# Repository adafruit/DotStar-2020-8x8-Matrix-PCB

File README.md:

## Adafruit DotStar High Density 8x8 Grid - 64 RGB LED Pixel Matrix PCB

<a href="http://www.adafruit.com/products/3444"><br/>
Click here to purchase one from the Adafruit shop</a>

PCB files for the Adafruit DotStar High Density 8x8 Grid - 64 RGB LED Pixel Matrix. Format is EagleCAD schematic and board layout
* https://www.adafruit.com/product/3444

### Description

Do not eat this LED grid just because it is so colorful and bite-sized! This is the tiniest little LED grid we could make, with 64 full RGB color pixels in a square that is only 1" by 1" square (thats 25.4mm x 25.4mm for you metric-lovers). Best of all, these are little DotStar LEDs, with built in PWM drivers, so you only need two digital I/O pins to get a-glowin'.

But do not be fooled by their small size, each LED is still incredibly, blindingly bright just like the DotStars/NeoPixels you know and love. These are the same integrated LEDs that are used in [our new fancy DotStar strips](https://www.adafruit.com/categories/885) just really small.

Arranged in an 8x8 matrix, each pixel is individually addressable: like NeoPixels, DotStar LEDs have an embedded microcontroller **inside the LED**. You can set the color/brightness of each LED to 24-bit color (8 bits each red green and blue). Each LED acts like a shift register, reading incoming color data on the input pins, and then shifting the previous color data out on the output pin. By sending a long string of data, you can control an 'infinite' number of LEDs. The PWM is built into each LED-chip so once you set the color you can stop talking to the disk and it will continue to PWM all the LEDs for you.

Wiring it up is easy: there are two 4-pad connection ports on the back. Solder wires to the input port (+5V GND ClockIn and DataIn) and provide 5VDC to the +5V and ground pins, then connect the CIN/DIN pin to your microcontroller. If you have hardware SPI, use the SCK and MOSI pins respectively. You'll also need to make a common ground from the 5V power supply to the microcontroller/Arduino. Since each LED can draw as much as 40mA (thats up to 2.5 Amps per panel if all LEDs are on bright white!) we suggest our 5V 2A power supply if you're going to use full brightness and a lot of white. For most uses, you'll see about 0.5A of current per panel, and you can set the brightness to drop that down. Note that so much current through a small board can make it toasty!

To keep the board small, we did not put any small surface-mount capacitors on the front. Instead, there's a power/ground pad set on the back and a 220uF capacitor that you can solder onto the back for a compact fit. There's also four mounting holes that you can use for attachment, or snap them off with pliers if you want a perfect 1" square.

[Check out our tutorial showing wiring, power usage calculations, example code for usage, etc!](https://learn.adafruit.com/adafruit-dotstar-leds)

### License

Adafruit invests time and resources providing this open source design, please support Adafruit and open-source hardware by purchasing products from [Adafruit](https://www.adafruit.com)!

Designed by Limor Fried/Ladyada for Adafruit Industries.

Creative Commons Attribution/Share-Alike, all text above must be included in any redistribution. See license.txt for additional details.

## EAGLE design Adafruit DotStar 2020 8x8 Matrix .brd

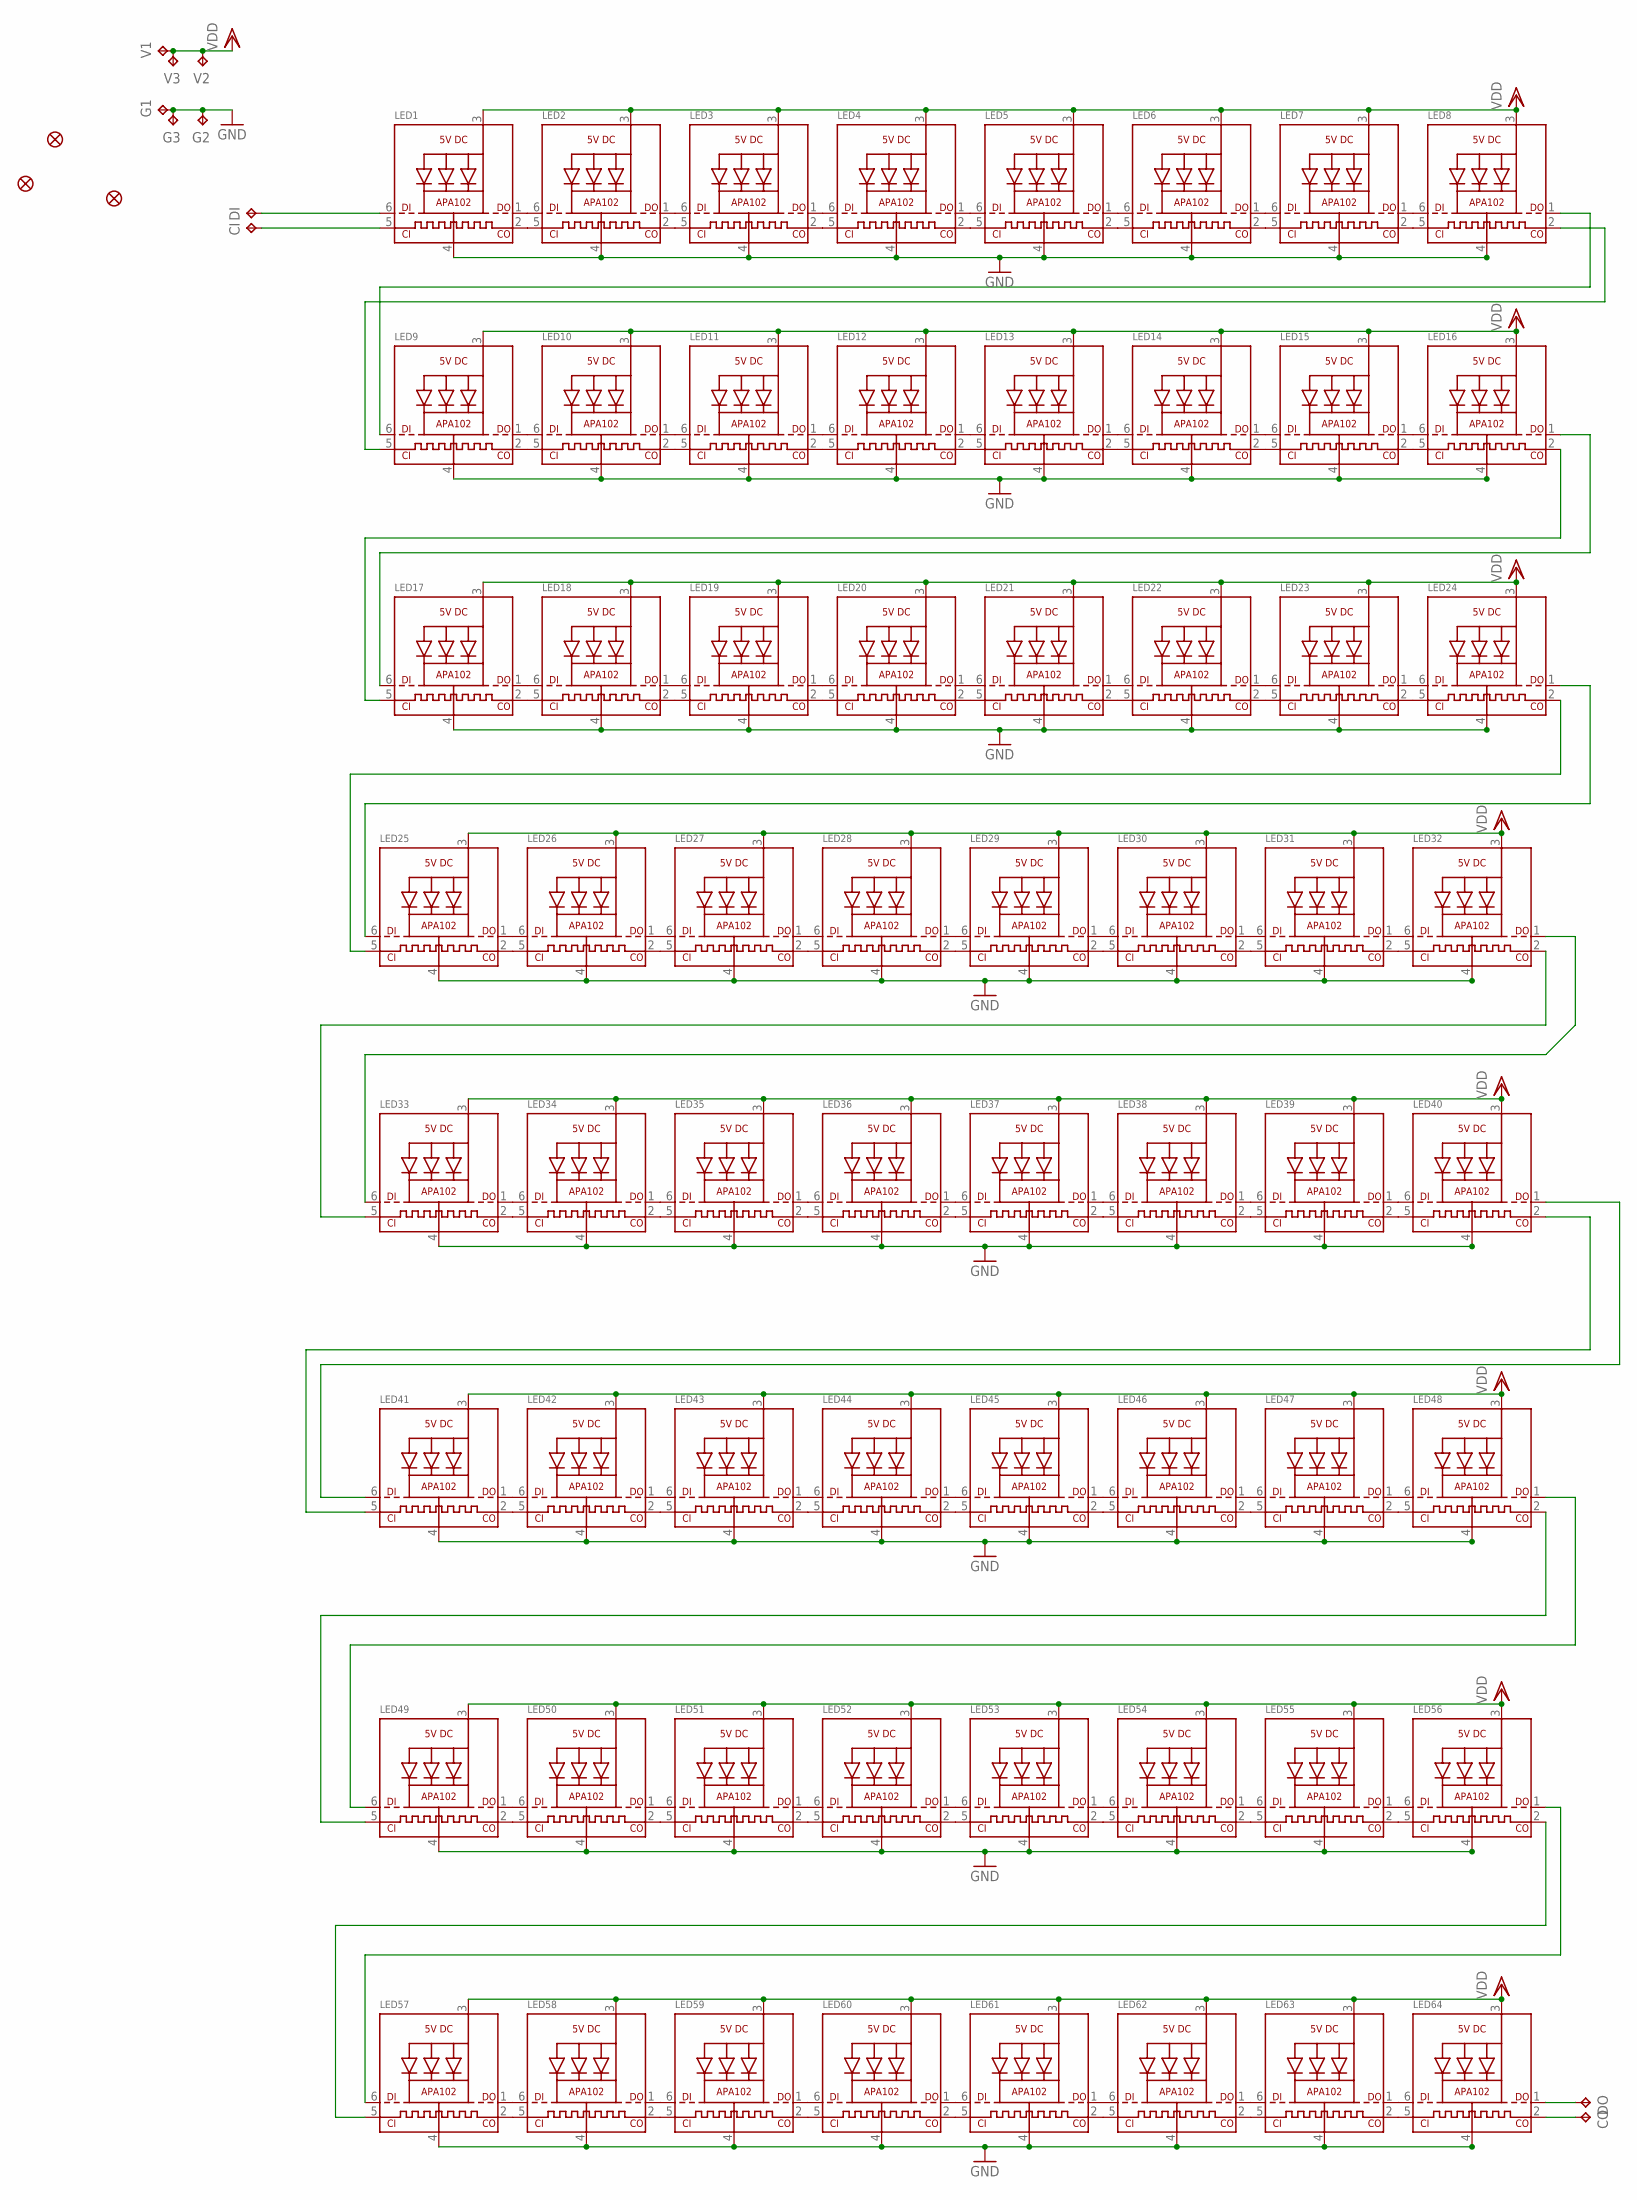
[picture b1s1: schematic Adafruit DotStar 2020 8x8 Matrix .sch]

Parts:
CI: TPTP20R; TP20R
CO: TPTP20R; TP20R
DI: TPTP20R; TP20R
DO: TPTP20R; TP20R
FID1, FID2, FID3: FIDUCIAL_0.5MM
G1, G2, G3: TPTP20R; TP20R
LED1, LED2, LED3, LED4, LED5, LED6, LED7, LED8, LED9, LED10, LED11, LED12, LED13, LED14, LED15, LED16, LED17, LED18, LED19, LED20, LED21, LED22, LED23, LED24, LED25, LED26, LED27, LED28, LED29, LED30, LED31, LED32, LED33, LED34, LED35, LED36, LED37, LED38, LED39, LED40, LED41, LED42, LED43, LED44, LED45, LED46, LED47, LED48, LED49, LED50, LED51, LED52, LED53, LED54, LED55, LED56, LED57, LED58, LED59, LED60, LED61, LED62, LED63, LED64: APA1022020; APA102_2020
V1, V2, V3: TPTP20R; TP20R

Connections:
C0: CO.TP, LED64.2 (CKO)
CIN: CI.TP, LED1.5 (CKI)
D0: DO.TP, LED64.1 (DO)
DIN: DI.TP, LED1.6 (DI)
GND: G1.TP, G2.TP, G3.TP, LED1.4 (GND), LED2.4 (GND), LED3.4 (GND), LED4.4 (GND), LED5.4 (GND), LED6.4 (GND), LED7.4 (GND), LED8.4 (GND), LED9.4 (GND), LED10.4 (GND), LED11.4 (GND), LED12.4 (GND), LED13.4 (GND), LED14.4 (GND), LED15.4 (GND), LED16.4 (GND), LED17.4 (GND), LED18.4 (GND), LED19.4 (GND), LED20.4 (GND), LED21.4 (GND), LED22.4 (GND), LED23.4 (GND), LED24.4 (GND), LED25.4 (GND), LED26.4 (GND), LED27.4 (GND), LED28.4 (GND), LED29.4 (GND), LED30.4 (GND), LED31.4 (GND), LED32.4 (GND), LED33.4 (GND), LED34.4 (GND), LED35.4 (GND), LED36.4 (GND), LED37.4 (GND), LED38.4 (GND), LED39.4 (GND), LED40.4 (GND), LED41.4 (GND), LED42.4 (GND), LED43.4 (GND), LED44.4 (GND), LED45.4 (GND), LED46.4 (GND), LED47.4 (GND), LED48.4 (GND), LED49.4 (GND), LED50.4 (GND), LED51.4 (GND), LED52.4 (GND), LED53.4 (GND), LED54.4 (GND), LED55.4 (GND), LED56.4 (GND), LED57.4 (GND), LED58.4 (GND), LED59.4 (GND), LED60.4 (GND), LED61.4 (GND), LED62.4 (GND), LED63.4 (GND), LED64.4 (GND)
unnamed: LED1.1 (DO), LED2.6 (DI)
unnamed: LED1.2 (CKO), LED2.5 (CKI)
unnamed: LED2.1 (DO), LED3.6 (DI)
unnamed: LED2.2 (CKO), LED3.5 (CKI)
unnamed: LED3.1 (DO), LED4.6 (DI)
unnamed: LED3.2 (CKO), LED4.5 (CKI)
unnamed: LED4.1 (DO), LED5.6 (DI)
unnamed: LED4.2 (CKO), LED5.5 (CKI)
unnamed: LED5.1 (DO), LED6.6 (DI)
unnamed: LED5.2 (CKO), LED6.5 (CKI)
unnamed: LED6.1 (DO), LED7.6 (DI)
unnamed: LED6.2 (CKO), LED7.5 (CKI)
unnamed: LED7.1 (DO), LED8.6 (DI)
unnamed: LED7.2 (CKO), LED8.5 (CKI)
unnamed: LED9.1 (DO), LED10.6 (DI)
unnamed: LED9.2 (CKO), LED10.5 (CKI)
unnamed: LED10.1 (DO), LED11.6 (DI)
unnamed: LED10.2 (CKO), LED11.5 (CKI)
unnamed: LED11.1 (DO), LED12.6 (DI)
unnamed: LED11.2 (CKO), LED12.5 (CKI)
unnamed: LED12.1 (DO), LED13.6 (DI)
unnamed: LED12.2 (CKO), LED13.5 (CKI)
unnamed: LED13.1 (DO), LED14.6 (DI)
unnamed: LED13.2 (CKO), LED14.5 (CKI)
unnamed: LED14.1 (DO), LED15.6 (DI)
unnamed: LED14.2 (CKO), LED15.5 (CKI)
unnamed: LED15.1 (DO), LED16.6 (DI)
unnamed: LED15.2 (CKO), LED16.5 (CKI)
unnamed: LED17.1 (DO), LED18.6 (DI)
unnamed: LED17.2 (CKO), LED18.5 (CKI)
unnamed: LED18.1 (DO), LED19.6 (DI)
unnamed: LED18.2 (CKO), LED19.5 (CKI)
unnamed: LED19.1 (DO), LED20.6 (DI)
unnamed: LED19.2 (CKO), LED20.5 (CKI)
unnamed: LED20.1 (DO), LED21.6 (DI)
unnamed: LED20.2 (CKO), LED21.5 (CKI)
unnamed: LED21.1 (DO), LED22.6 (DI)
unnamed: LED21.2 (CKO), LED22.5 (CKI)
unnamed: LED22.1 (DO), LED23.6 (DI)
unnamed: LED22.2 (CKO), LED23.5 (CKI)
unnamed: LED23.1 (DO), LED24.6 (DI)
unnamed: LED23.2 (CKO), LED24.5 (CKI)
unnamed: LED25.1 (DO), LED26.6 (DI)
unnamed: LED25.2 (CKO), LED26.5 (CKI)
unnamed: LED26.1 (DO), LED27.6 (DI)
unnamed: LED26.2 (CKO), LED27.5 (CKI)
unnamed: LED27.1 (DO), LED28.6 (DI)
unnamed: LED27.2 (CKO), LED28.5 (CKI)
unnamed: LED28.1 (DO), LED29.6 (DI)
unnamed: LED28.2 (CKO), LED29.5 (CKI)
unnamed: LED29.1 (DO), LED30.6 (DI)
unnamed: LED29.2 (CKO), LED30.5 (CKI)
unnamed: LED30.1 (DO), LED31.6 (DI)
unnamed: LED30.2 (CKO), LED31.5 (CKI)
unnamed: LED31.1 (DO), LED32.6 (DI)
unnamed: LED31.2 (CKO), LED32.5 (CKI)
unnamed: LED33.1 (DO), LED34.6 (DI)
unnamed: LED33.2 (CKO), LED34.5 (CKI)
unnamed: LED34.1 (DO), LED35.6 (DI)
unnamed: LED34.2 (CKO), LED35.5 (CKI)
unnamed: LED35.1 (DO), LED36.6 (DI)
unnamed: LED35.2 (CKO), LED36.5 (CKI)
unnamed: LED36.1 (DO), LED37.6 (DI)
unnamed: LED36.2 (CKO), LED37.5 (CKI)
unnamed: LED37.1 (DO), LED38.6 (DI)
unnamed: LED37.2 (CKO), LED38.5 (CKI)
unnamed: LED38.1 (DO), LED39.6 (DI)
unnamed: LED38.2 (CKO), LED39.5 (CKI)
unnamed: LED39.1 (DO), LED40.6 (DI)
unnamed: LED39.2 (CKO), LED40.5 (CKI)
unnamed: LED41.1 (DO), LED42.6 (DI)
unnamed: LED41.2 (CKO), LED42.5 (CKI)
unnamed: LED42.1 (DO), LED43.6 (DI)
unnamed: LED42.2 (CKO), LED43.5 (CKI)
unnamed: LED43.1 (DO), LED44.6 (DI)
unnamed: LED43.2 (CKO), LED44.5 (CKI)
unnamed: LED44.1 (DO), LED45.6 (DI)
unnamed: LED44.2 (CKO), LED45.5 (CKI)
unnamed: LED45.1 (DO), LED46.6 (DI)
unnamed: LED45.2 (CKO), LED46.5 (CKI)
unnamed: LED46.1 (DO), LED47.6 (DI)
unnamed: LED46.2 (CKO), LED47.5 (CKI)
unnamed: LED47.1 (DO), LED48.6 (DI)
unnamed: LED47.2 (CKO), LED48.5 (CKI)
unnamed: LED49.1 (DO), LED50.6 (DI)
unnamed: LED49.2 (CKO), LED50.5 (CKI)
unnamed: LED50.1 (DO), LED51.6 (DI)
unnamed: LED50.2 (CKO), LED51.5 (CKI)
unnamed: LED51.1 (DO), LED52.6 (DI)
unnamed: LED51.2 (CKO), LED52.5 (CKI)
unnamed: LED52.1 (DO), LED53.6 (DI)
unnamed: LED52.2 (CKO), LED53.5 (CKI)
unnamed: LED53.1 (DO), LED54.6 (DI)
unnamed: LED53.2 (CKO), LED54.5 (CKI)
unnamed: LED54.1 (DO), LED55.6 (DI)
unnamed: LED54.2 (CKO), LED55.5 (CKI)
unnamed: LED55.1 (DO), LED56.6 (DI)
unnamed: LED55.2 (CKO), LED56.5 (CKI)
unnamed: LED57.1 (DO), LED58.6 (DI)
unnamed: LED57.2 (CKO), LED58.5 (CKI)
unnamed: LED58.1 (DO), LED59.6 (DI)
unnamed: LED58.2 (CKO), LED59.5 (CKI)
unnamed: LED59.1 (DO), LED60.6 (DI)
unnamed: LED59.2 (CKO), LED60.5 (CKI)
unnamed: LED60.1 (DO), LED61.6 (DI)
unnamed: LED60.2 (CKO), LED61.5 (CKI)
unnamed: LED61.1 (DO), LED62.6 (DI)
unnamed: LED61.2 (CKO), LED62.5 (CKI)
unnamed: LED62.1 (DO), LED63.6 (DI)
unnamed: LED62.2 (CKO), LED63.5 (CKI)
unnamed: LED63.1 (DO), LED64.6 (DI)
unnamed: LED63.2 (CKO), LED64.5 (CKI)
unnamed: LED8.1 (DO), LED9.6 (DI)
unnamed: LED8.2 (CKO), LED9.5 (CKI)
unnamed: LED16.1 (DO), LED17.6 (DI)
unnamed: LED16.2 (CKO), LED17.5 (CKI)
unnamed: LED24.1 (DO), LED25.6 (DI)
unnamed: LED24.2 (CKO), LED25.5 (CKI)
unnamed: LED32.1 (DO), LED33.6 (DI)
unnamed: LED32.2 (CKO), LED33.5 (CKI)
unnamed: LED56.1 (DO), LED57.6 (DI)
unnamed: LED56.2 (CKO), LED57.5 (CKI)
unnamed: LED48.2 (CKO), LED49.5 (CKI)
unnamed: LED48.1 (DO), LED49.6 (DI)
unnamed: LED40.2 (CKO), LED41.5 (CKI)
unnamed: LED40.1 (DO), LED41.6 (DI)
VDD: LED1.3 (VDD), LED2.3 (VDD), LED3.3 (VDD), LED4.3 (VDD), LED5.3 (VDD), LED6.3 (VDD), LED7.3 (VDD), LED8.3 (VDD), LED9.3 (VDD), LED10.3 (VDD), LED11.3 (VDD), LED12.3 (VDD), LED13.3 (VDD), LED14.3 (VDD), LED15.3 (VDD), LED16.3 (VDD), LED17.3 (VDD), LED18.3 (VDD), LED19.3 (VDD), LED20.3 (VDD), LED21.3 (VDD), LED22.3 (VDD), LED23.3 (VDD), LED24.3 (VDD), LED25.3 (VDD), LED26.3 (VDD), LED27.3 (VDD), LED28.3 (VDD), LED29.3 (VDD), LED30.3 (VDD), LED31.3 (VDD), LED32.3 (VDD), LED33.3 (VDD), LED34.3 (VDD), LED35.3 (VDD), LED36.3 (VDD), LED37.3 (VDD), LED38.3 (VDD), LED39.3 (VDD), LED40.3 (VDD), LED41.3 (VDD), LED42.3 (VDD), LED43.3 (VDD), LED44.3 (VDD), LED45.3 (VDD), LED46.3 (VDD), LED47.3 (VDD), LED48.3 (VDD), LED49.3 (VDD), LED50.3 (VDD), LED51.3 (VDD), LED52.3 (VDD), LED53.3 (VDD), LED54.3 (VDD), LED55.3 (VDD), LED56.3 (VDD), LED57.3 (VDD), LED58.3 (VDD), LED59.3 (VDD), LED60.3 (VDD), LED61.3 (VDD), LED62.3 (VDD), LED63.3 (VDD), LED64.3 (VDD), V1.TP, V2.TP, V3.TP

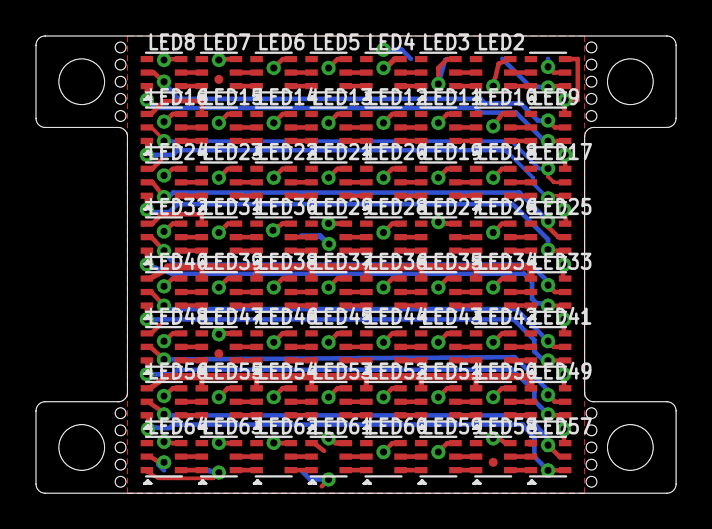
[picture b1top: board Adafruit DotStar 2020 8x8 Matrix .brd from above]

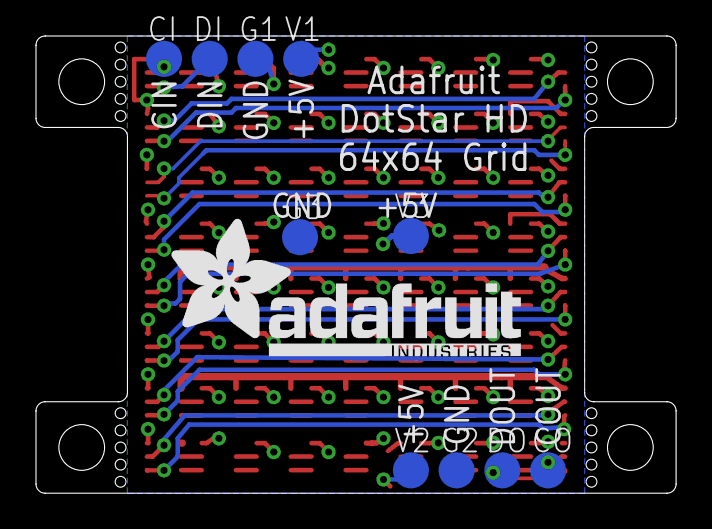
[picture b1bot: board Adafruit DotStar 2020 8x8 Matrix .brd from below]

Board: 2 copper layers, 35.6 x 25.4 mm, 78 parts (11 on the bottom side), 132 nets.

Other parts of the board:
U$1: ADAFRUIT_TEXT_20MM

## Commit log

2018-05-20 filez
2019-07-16 updated to use cookiecutter for pcb repos

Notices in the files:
parts and their libraries:
microbuilder: This work is placed in the public domain, and may be freely used for commercial and non-commercial work with the following conditions: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
